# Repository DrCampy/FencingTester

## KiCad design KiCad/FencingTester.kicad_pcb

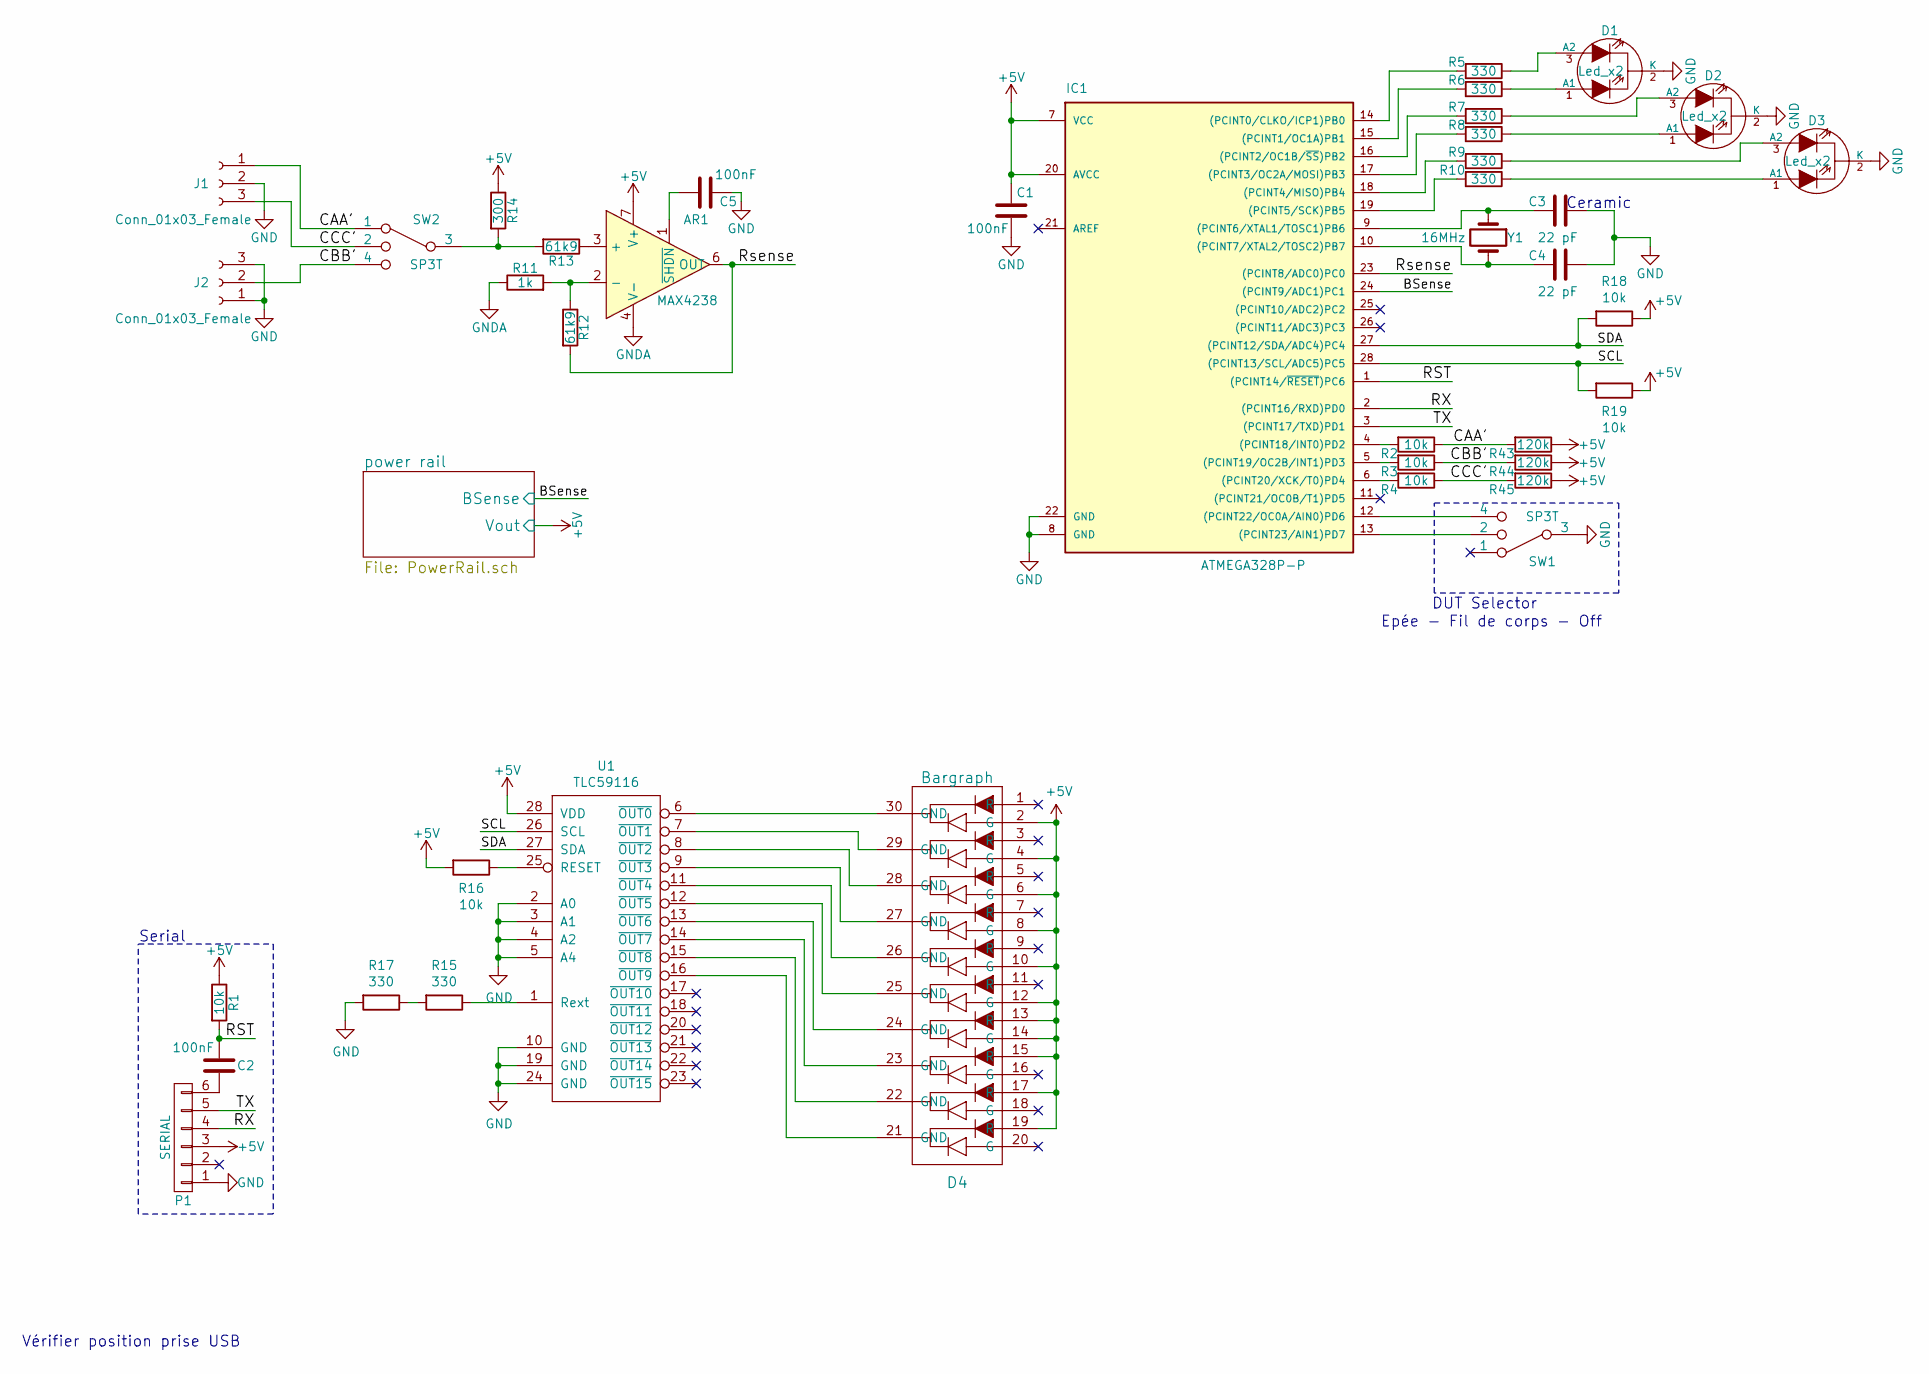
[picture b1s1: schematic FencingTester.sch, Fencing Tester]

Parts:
AR1: MAX4238; SOIC-8_3.9x4.9mm_P1.27mm
C1, C2, C5: 100nF; C_0805_2012Metric_Pad1.15x1.40mm_HandSolder
C3, C4: 22 pF; C_0805_2012Metric_Pad1.15x1.40mm_HandSolder
D1, D2, D3: Led_x2; 3PadsWires
D4: Bargraph
IC1: ATMEGA328P-P; DIP-28_W7.62mm_Socket_LongPads
J1, J2: Conn_01x03_Female; 3PadsWires
P1: SERIAL; PinHeader_1x06_P2.54mm_Vertical
R1, R2, R3, R4, R16, R18, R19: 10k; R_0805_2012Metric_Pad1.15x1.40mm_HandSolder
R5, R6, R7, R8, R9, R10, R15, R17: 330; R_0805_2012Metric_Pad1.15x1.40mm_HandSolder
R11: 1k; R_0805_2012Metric_Pad1.15x1.40mm_HandSolder
R12, R13: 61k9; R_0805_2012Metric_Pad1.15x1.40mm_HandSolder
R14: 300; R_0805_2012Metric_Pad1.15x1.40mm_HandSolder
R43, R44, R45: 120k; R_0805_2012Metric_Pad1.15x1.40mm_HandSolder
SW1: SP3T; SW1
SW2: SP3T; SW2
U1: TLC59116; TSSOP-28_4.4x9.7mm_P0.65mm
Y1: 16MHz; Quartz

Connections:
+5V: AR1.7 (V+), C1.1, D4.2 (G), D4.4 (G), D4.6 (G), D4.8 (G), D4.10 (G), D4.12 (G), D4.13 (R), D4.14 (G), D4.15 (R), D4.17 (R), D4.19 (R), IC1.7 (VCC), IC1.20 (AVCC), P1.3, R1.1, R14.1, R16.2, R18.1, R19.1, R43.1, R44.1, R45.1, U1.28 (VDD); also elsewhere on the board
/BSense: IC1.24 ((PCINT9/ADC1)PC1); also elsewhere on the board
/CAA': J1.1, R2.1, R43.2, SW2.1
/CBB': J2.2, R3.1, R44.2, SW2.4
/CCC': J1.3, R4.1, R45.2, SW2.2
/RST: C2.2, IC1.1 ((PCINT14/~RESET~)PC6), R1.2
/RX: IC1.2 ((PCINT16/RXD)PD0), P1.4
/Rsense: AR1.6 (OUT), IC1.23 ((PCINT8/ADC0)PC0), R12.2
/SCL: IC1.28 ((PCINT13/SCL/ADC5)PC5), R19.2, U1.26 (SCL)
/SDA: IC1.27 ((PCINT12/SDA/ADC4)PC4), R18.2, U1.27 (SDA)
/TX: IC1.3 ((PCINT17/TXD)PD1), P1.5
GND: C1.2, C3.2, C4.2, C5.1, D1.2 (K), D2.2 (K), D3.2 (K), IC1.8 (GND), IC1.22 (GND), J1.2, J2.1, J2.3, P1.1, R17.2, SW1.3, U1.2 (A0), U1.3 (A1), U1.4 (A2), U1.5 (A4), U1.10 (GND), U1.19 (GND), U1.24 (GND); also elsewhere on the board
GNDA: AR1.4 (V-), R11.1; also elsewhere on the board
unnamed: AR1.1 (~SHDN), C5.2
unnamed: AR1.2 (-), R11.2, R12.1
unnamed: AR1.3 (+), R13.1
unnamed: C2.1, P1.6
unnamed: C3.1, IC1.9 ((PCINT6/XTAL1/TOSC1)PB6), Y1.1
unnamed: C4.1, IC1.10 ((PCINT7/XTAL2/TOSC2)PB7), Y1.2
unnamed: D1.1 (A1), R6.1
unnamed: D1.3 (A2), R5.1
unnamed: D2.1 (A1), R8.1
unnamed: D2.3 (A2), R7.1
unnamed: D3.1 (A1), R10.1
unnamed: D3.3 (A2), R9.1
unnamed: D4.21 (GND), U1.16 (~OUT9)
unnamed: D4.22 (GND), U1.15 (~OUT8)
unnamed: D4.23 (GND), U1.14 (~OUT7)
unnamed: D4.24 (GND), U1.13 (~OUT6)
unnamed: D4.25 (GND), U1.12 (~OUT5)
unnamed: D4.26 (GND), U1.11 (~OUT4)
unnamed: D4.27 (GND), U1.9 (~OUT3)
unnamed: D4.28 (GND), U1.8 (~OUT2)
unnamed: D4.29 (GND), U1.7 (~OUT1)
unnamed: D4.30 (GND), U1.6 (~OUT0)
unnamed: IC1.4 ((PCINT18/INT0)PD2), R2.2
unnamed: IC1.5 ((PCINT19/OC2B/INT1)PD3), R3.2
unnamed: IC1.6 ((PCINT20/XCK/T0)PD4), R4.2
unnamed: IC1.12 ((PCINT22/OC0A/AIN0)PD6), SW1.4
unnamed: IC1.13 ((PCINT23/AIN1)PD7), SW1.2
unnamed: IC1.14 ((PCINT0/CLKO/ICP1)PB0), R5.2
unnamed: IC1.15 ((PCINT1/OC1A)PB1), R6.2
unnamed: IC1.16 ((PCINT2/OC1B/~SS~)PB2), R7.2
unnamed: IC1.17 ((PCINT3/OC2A/MOSI)PB3), R8.2
unnamed: IC1.18 ((PCINT4/MISO)PB4), R9.2
unnamed: IC1.19 ((PCINT5/SCK)PB5), R10.2
unnamed: R13.2, R14.2, SW2.3
unnamed: R15.1, U1.1 (Rext)
unnamed: R15.2, R17.1
unnamed: R16.1, U1.25 (RESET)

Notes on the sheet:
Ceramic
Serial
DUT Selector
Epée - Fil de corps - Off
Vérifier position prise USB

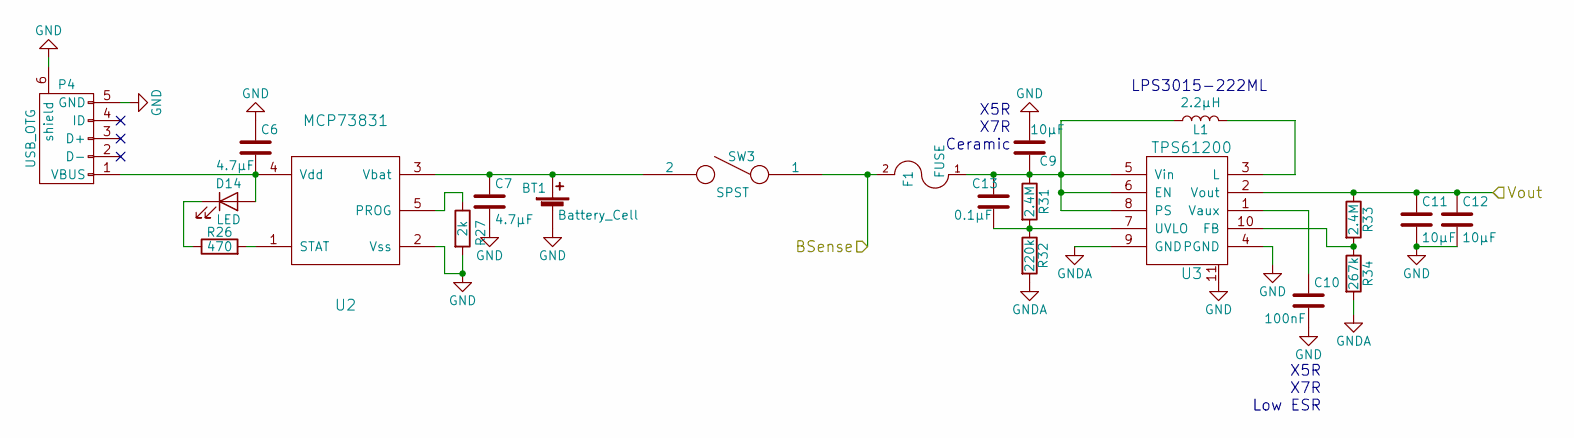
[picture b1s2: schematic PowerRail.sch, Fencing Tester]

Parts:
BT1: Battery_Cell; 2PadsWire
C6, C7: 4.7µF; C_0805_2012Metric_Pad1.15x1.40mm_HandSolder
C9, C11, C12: 10µF; C_0805_2012Metric_Pad1.15x1.40mm_HandSolder
C10: 100nF; C_0805_2012Metric_Pad1.15x1.40mm_HandSolder
C13: 0.1µF; C_0805_2012Metric_Pad1.15x1.40mm_HandSolder
D14: LED; ChargingLed
F1: FUSE; Fuse_1206_3216Metric_Pad1.42x1.75mm_HandSolder
L1: 2.2µH; CoilCraft-LPS3015-CMS
P4: USB_OTG; USB_Micro-B
R26: 470; R_0805_2012Metric_Pad1.15x1.40mm_HandSolder
R27: 2k; R_0805_2012Metric_Pad1.15x1.40mm_HandSolder
R31, R33: 2.4M; R_0805_2012Metric_Pad1.15x1.40mm_HandSolder
R32: 220k; R_0805_2012Metric_Pad1.15x1.40mm_HandSolder
R34: 267k; R_0805_2012Metric_Pad1.15x1.40mm_HandSolder
SW3: SPST; SW3
U2: MCP73831; TSOT-23-5_HandSoldering
U3: TPS61200

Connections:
+5V: C11.1, C12.1, R33.1, U3.2 (Vout); also elsewhere on the board
/BSense: F1.2, SW3.1; also elsewhere on the board
GND: BT1.2 (-), C6.1, C7.2, C9.1, C10.2, C11.2, C12.2, P4.5 (GND), P4.6 (shield), R27.2, U2.2 (Vss), U3.4 (PGND), U3.11; also elsewhere on the board
GNDA: R32.2, R34.2, U3.9 (GND); also elsewhere on the board
unnamed: BT1.1 (+), C7.1, SW3.2, U2.3 (Vbat)
unnamed: C6.2, D14.2 (A), P4.1 (VBUS), U2.4 (Vdd)
unnamed: C10.1, U3.1 (Vaux)
unnamed: C9.2, C13.1, F1.1, L1.1, R31.1, U3.5 (Vin), U3.6 (EN), U3.8 (PS)
unnamed: C13.2, R31.2, R32.1, U3.7 (UVLO)
unnamed: D14.1 (K), R26.1
unnamed: L1.2, U3.3 (L)
unnamed: R26.2, U2.1 (STAT)
unnamed: R27.1, U2.5 (PROG)
unnamed: R33.2, R34.1, U3.10 (FB)

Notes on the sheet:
X5R X7R Ceramic
X5R X7R Low ESR
LPS3015-222ML

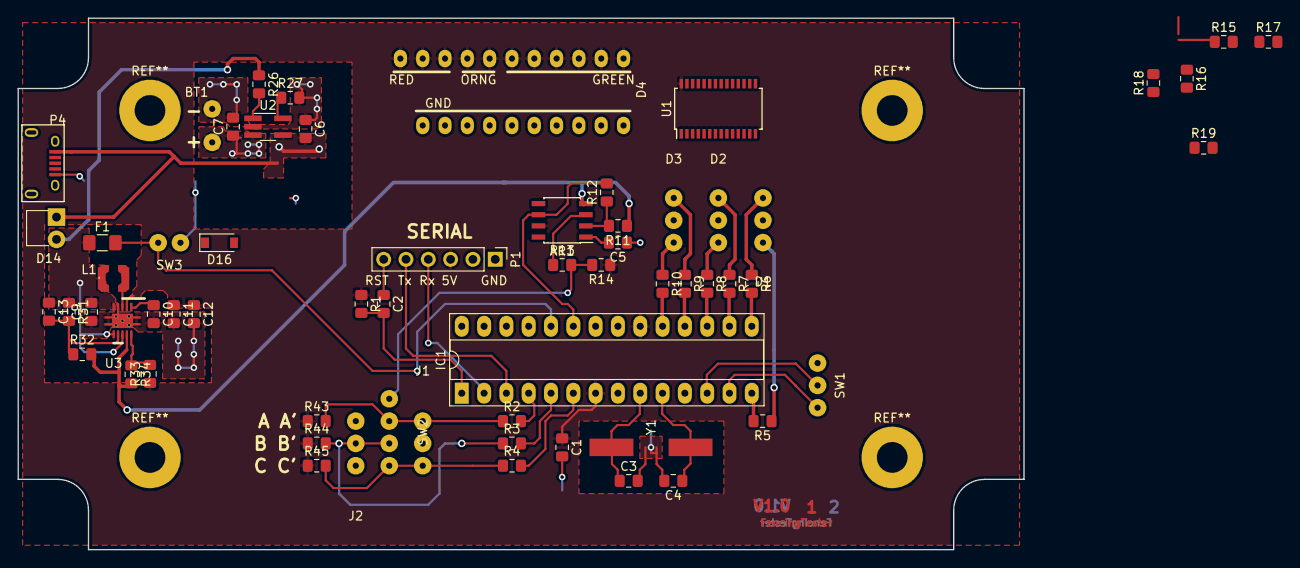
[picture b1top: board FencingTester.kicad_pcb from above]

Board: 2 copper layers, 114.5 x 60.5 mm, 62 parts (0 on the bottom side), 60 nets.

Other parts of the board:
D16: D_Schottky; SOD-123

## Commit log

2018-09-04 Project import
    Importing project from Dropbox
2018-09-04 Import
    Importing project from Dropbox
2018-09-08 General update
    Upgrading Kicad Project to V5.0.0
    Deleting old files
2018-09-08 Deleting duplicate kicad folder
2018-09-11 Schottky diode Datasheet
2018-09-15 New Mosfet designe Bargraph driver
2018-09-15 Bargraph driver - Mosfet
2018-09-20 Finishing MOSFET implementation on Bargraph driver
    Swithcing from BJT to mosfet. Simplifying the use of diodes
2018-09-20 New PCB Layout
    New pcb layout for the bargraph driver part
2018-10-09 Wiring PCB
2018-10-26 Spice simulations
    Spice simulations for bargraph
2018-10-27 Sheet bargraph driver marked unused
2018-10-27 Simplifying power rail
    We do not switch to USB power anymore when USB is connected
2018-10-27 Adding new components
2018-10-27 New bargraph driver + General cleanup
2018-10-27 kicad project edits
2018-10-27 new netlist generated
2018-10-27 Importing new netlist
2018-10-27 Notes on how to use I2C with atmega
2018-10-27 LT Spice simulations
2018-10-27 kicad files
2018-10-27 More notes on I2C
2018-11-01 Finishing bargraph init
2018-11-06 Calculs I2C SCL_Freq
2018-11-07 Bargraph::setValue coding using I2C
2018-11-07 Update Schematic
2018-11-07 Update Netlist
2018-11-07 update bak files
2018-11-07 Update PCB
2018-11-07 Deleting unnecessary file
2018-11-07 Delete (Copie en conflit de DESKTOP-UJQC2R6 2017-02-15).atsuo
    unnecessary file
2018-11-07 Delete .atsuo
    unnecessary file
2018-11-07 Deleting unnecessary file
    Covered by gitignore
2018-11-07 Deleting .atsuo
    unnecessary file
2018-11-07 Deleting unnecessary files
    In gitignore
2018-11-08 Removing Channel class
    deprecated files
2019-09-30 Updating modules libraries
2019-09-30 Adding new notes
2019-10-01 PCB advancements
2019-10-11 [WIP] PCB layout
2019-10-11 Ignore bak files
